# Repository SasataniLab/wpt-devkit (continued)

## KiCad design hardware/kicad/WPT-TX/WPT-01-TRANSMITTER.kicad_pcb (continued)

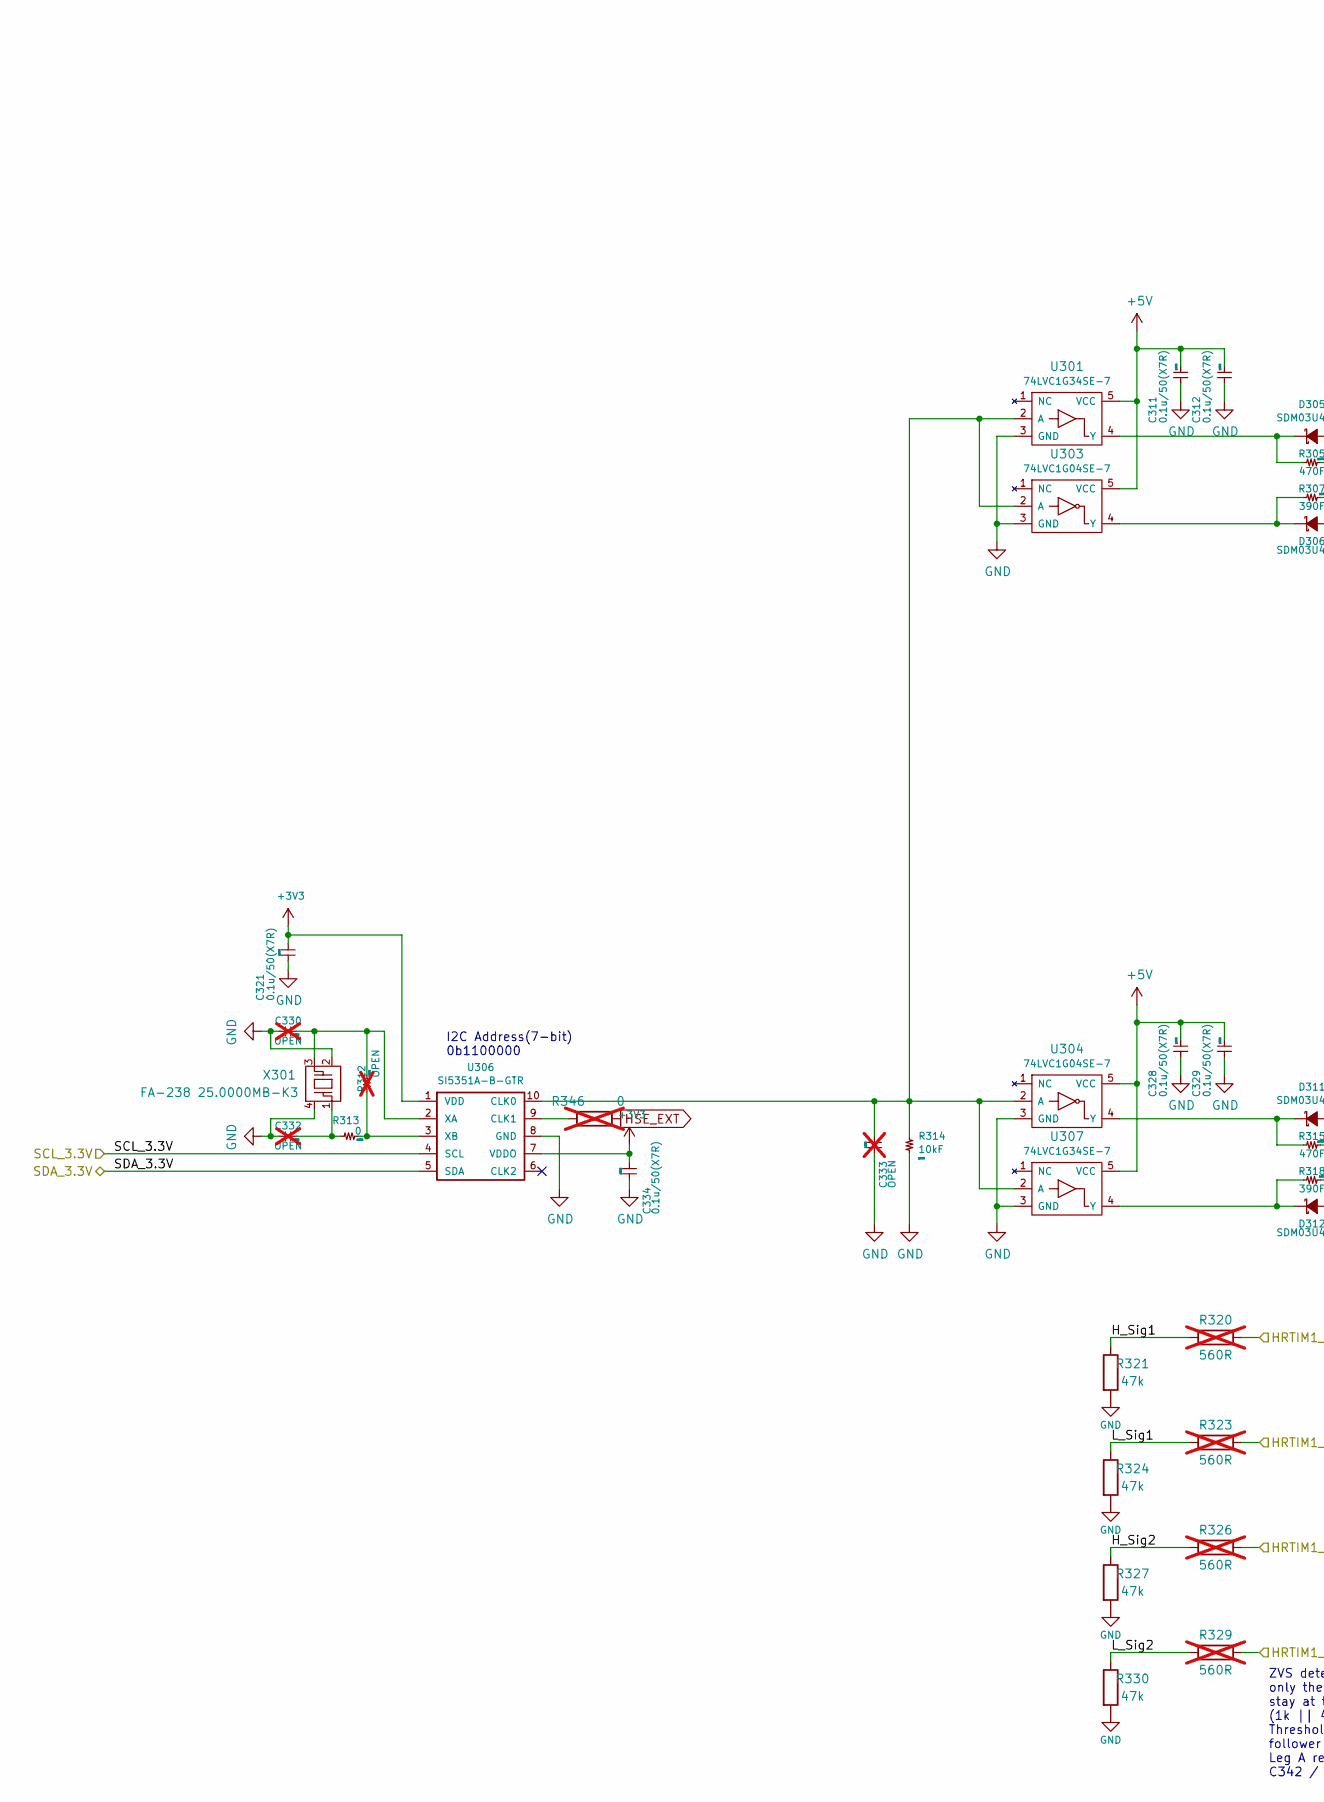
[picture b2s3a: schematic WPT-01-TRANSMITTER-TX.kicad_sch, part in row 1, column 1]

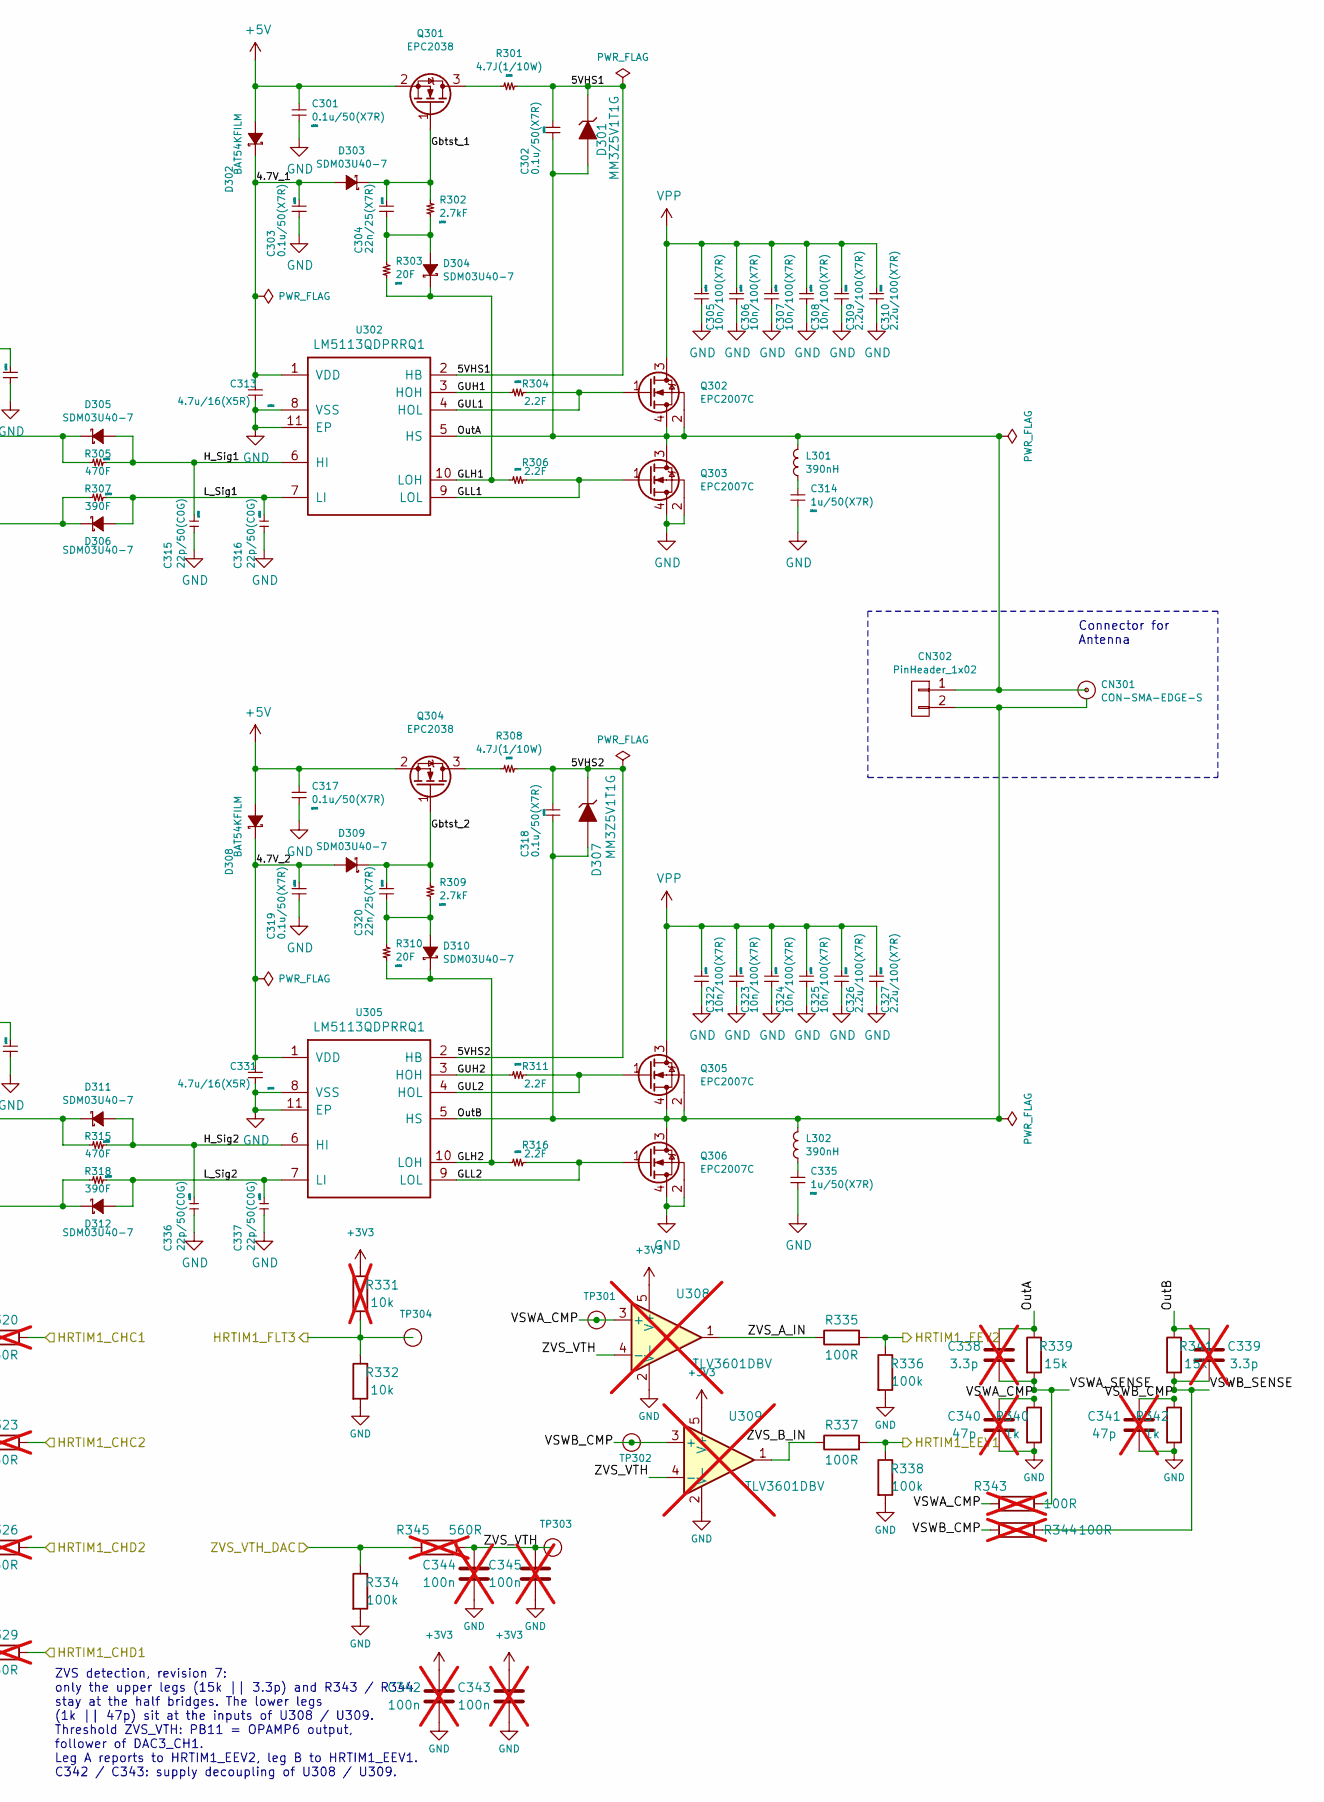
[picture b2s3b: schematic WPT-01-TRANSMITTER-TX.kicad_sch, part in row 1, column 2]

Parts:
C301, C302, C303, C311, C312, C317, C318, C319, C321, C328, C329, C334: 0.1u/50(X7R); GRM15; Manufacturer Part Number GCM155R71H104KE02D
C304, C320: 22n/25(X7R); GRM15; Manufacturer Part Number CC0402KRX7R8BB223
C305, C306, C307, C308, C322, C323, C324, C325: 10n/100(X7R); GRM18; Manufacturer Part Number CL10B103KC8WPNC
C309, C310, C326, C327: 2.2u/100(X7R); GRM32; Manufacturer Part Number CL32B225KCJZW6E
C313, C331: 4.7u/16(X5R); GRM15; Manufacturer Part Number CL05A475MO5NUNC
C314, C335: 1u/50(X7R); GRM21; Manufacturer Part Number CL21B105KBFNNNG
C315, C316, C336, C337: 22p/50(C0G); GRM15; Manufacturer Part Number GCM1555C1H220JA16D
C330, C332: OPEN; GRM15; Manufacturer Part Number GRM15; not fitted
C333: OPEN; GRM15; Manufacturer Part Number CC0402; not fitted
C338, C339: 3.3p; C_0402_1005Metric; Manufacturer Part Number GJM1555C1H3R3BB01D; not fitted
C340, C341: 47p; C_0402_1005Metric; Manufacturer Part Number GCM1555C1H470GA16D; not fitted
C342, C343, C344, C345: 100n; C_0402_1005Metric; Manufacturer Part Number GCM155R71H104KE02D; not fitted
CN301: CON-SMA-EDGE-S; Manufacturer Part Number CON-SMA-EDGE-S
CN302: PinHeader_1x02; ULO-PH409-1x2SX1; Manufacturer Part Number 61300211121
D301, D307: MM3Z5V1T1G; SOD-323; Manufacturer Part Number MM3Z5V1T1G
D302, D308: BAT54KFILM; SOD-523F_STMicroelectronics; Manufacturer Part Number BAT54KFILM
D303, D304, D305, D306, D309, D310, D311, D312: SDM03U40-7; SOD-523F_Diodes; Manufacturer Part Number SDM03U40-7
L301, L302: 390nH; 2929SQ; Manufacturer Part Number 2929SQ-391JEC
Q301, Q304: EPC2038; Manufacturer Part Number EPC2038
Q302, Q303, Q305, Q306: EPC2007C; Manufacturer Part Number EPC2007C
R301, R308: 4.7J(1/10W); R_0402; Manufacturer Part Number ERJ-2GEJ4R7X
R302, R309: 2.7kF; R_0402; Manufacturer Part Number RC0402FR-072K7L
R303, R310: 20F; R_0402; Manufacturer Part Number RC0402FR-0720RL
R304, R306, R311, R316: 2.2F; R_0402; Manufacturer Part Number RC0402FR-072R2L
R305, R315: 470F; R_0603; Manufacturer Part Number RC0603FR-07470RL
R307, R318: 390F; R_0603; Manufacturer Part Number RC0603FR-07390RL
R312: OPEN; R_0402; Manufacturer Part Number RC0402; not fitted
R313: 0; R_0402; Manufacturer Part Number RC0402FR-070RL
R314: 10kF; R_0402; Manufacturer Part Number RC0402FR-0710KL
R320, R323, R326, R329, R345: 560R; R_0402_1005Metric; Manufacturer Part Number RC0402FR-07560RL; not fitted
R321, R324, R327, R330: 47k; R_0402_1005Metric; Manufacturer Part Number RC0402FR-0747KL
R331: 10k; R_0402_1005Metric; Manufacturer Part Number RC0402FR-0710KL; not fitted
R332: 10k; R_0402_1005Metric; Manufacturer Part Number RC0402FR-0710KL
R334, R336, R338: 100k; R_0402_1005Metric; Manufacturer Part Number RC0402FR-07100KL
R335, R337: 100R; R_0402_1005Metric; Manufacturer Part Number RC0402FR-07100RL
R339, R341: 15k; R_0402_1005Metric; Manufacturer Part Number ERJ-PA2F1502X
R340, R342: 1k; R_0402_1005Metric; Manufacturer Part Number RC0402FR-071KL
R343, R344: 100R; R_0402_1005Metric; Manufacturer Part Number RC0402FR-07100RL; not fitted
R346: 0; R_0402_1005Metric; Manufacturer Part Number RC0402FR-070RL; not fitted
TP301, TP302, TP303, TP304: TP1.0; TP_1mm
U301, U307: 74LVC1G34SE-7; SOT-353_SC-70-5_Diodes; Manufacturer Part Number 74LVC1G34SE-7
U302, U305: LM5113QDPRRQ1; Texas_S-PWSON-N10_ThermalVias; Manufacturer Part Number LM5113QDPRRQ1
U303, U304: 74LVC1G04SE-7; SOT-353_SC-70-5_Diodes; Manufacturer Part Number 74LVC1G04SE-7
U306: SI5351A-B-GTR; Siliconlabs_MSOP-10_3x3mm_Pitch0.5mm; Manufacturer Part Number SI5351A-B-GTR
U308, U309: TLV3601DBV; SOT-23-5; Manufacturer Part Number TLV3601DBVR; not fitted
X301: FA-238 25.0000MB-K3; FA-238; Manufacturer Part Number FA-238 25.0000MB-K3

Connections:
+3V3: C321.1, C334.1, C342.1, C343.1, R331.1, U306.1 (VDD), U306.7 (VDDO), U308.5 (V+), U309.5 (V+); also elsewhere on the board
+5V: C301.1, C311.1, C312.1, C317.1, C328.1, C329.1, D302.2 (A), D308.2 (A), Q301.2 (S), Q304.2 (S), U301.5 (VCC), U303.5 (VCC), U304.5 (VCC), U307.5 (VCC); also elsewhere on the board
/HRTIM1_CHC1: R320.2; also elsewhere on the board
/HRTIM1_CHC2: R323.2; also elsewhere on the board
/HRTIM1_CHD1: R329.2; also elsewhere on the board
/HRTIM1_CHD2: R326.2; also elsewhere on the board
/HRTIM1_EEV1: R337.2, R338.1; also elsewhere on the board
/HRTIM1_EEV2: R335.2, R336.1; also elsewhere on the board
/HRTIM1_FLT3: R331.2, R332.1, TP304.1; also elsewhere on the board
/WPT-01-TRANSMITTER-POWER/SCL_3.3V: U306.4 (SCL); also elsewhere on the board
/WPT-01-TRANSMITTER-POWER/SDA_3.3V: U306.5 (SDA); also elsewhere on the board
/WPT-01-TRANSMITTER-TX/4.7V_1: C303.1, C313.1, D302.1 (C), D303.2 (A), U302.1 (VDD)
/WPT-01-TRANSMITTER-TX/4.7V_2: C319.1, C331.1, D308.1 (C), D309.2 (A), U305.1 (VDD)
/WPT-01-TRANSMITTER-TX/5VHS1: C302.1, D301.1 (K), R301.1, U302.2 (HB)
/WPT-01-TRANSMITTER-TX/5VHS2: C318.1, D307.1 (K), R308.1, U305.2 (HB)
/WPT-01-TRANSMITTER-TX/GLH1: D304.1 (C), R303.1, R306.2, U302.10 (LOH)
/WPT-01-TRANSMITTER-TX/GLH2: D310.1 (C), R310.1, R316.2, U305.10 (LOH)
/WPT-01-TRANSMITTER-TX/GLL1: Q303.1 (G), R306.1, U302.9 (LOL)
/WPT-01-TRANSMITTER-TX/GLL2: Q306.1 (G), R316.1, U305.9 (LOL)
/WPT-01-TRANSMITTER-TX/GUH1: R304.2, U302.3 (HOH)
/WPT-01-TRANSMITTER-TX/GUH2: R311.2, U305.3 (HOH)
/WPT-01-TRANSMITTER-TX/GUL1: Q302.1 (G), R304.1, U302.4 (HOL)
/WPT-01-TRANSMITTER-TX/GUL2: Q305.1 (G), R311.1, U305.4 (HOL)
/WPT-01-TRANSMITTER-TX/Gbtst_1: C304.1, D303.1 (C), Q301.1 (G), R302.2
/WPT-01-TRANSMITTER-TX/Gbtst_2: C320.1, D309.1 (C), Q304.1 (G), R309.2
/WPT-01-TRANSMITTER-TX/H_Sig1: C315.1, D305.2 (A), R305.1, R320.1, R321.1, U302.6 (HI)
/WPT-01-TRANSMITTER-TX/H_Sig2: C336.1, D311.2 (A), R315.1, R326.1, R327.1, U305.6 (HI)
/WPT-01-TRANSMITTER-TX/L_Sig1: C316.1, D306.2 (A), R307.1, R323.1, R324.1, U302.7 (LI)
/WPT-01-TRANSMITTER-TX/L_Sig2: C337.1, D312.2 (A), R318.1, R329.1, R330.1, U305.7 (LI)
/WPT-01-TRANSMITTER-TX/OutA: C302.2, C338.1, CN301.1, CN302.1, D301.2 (A), L301.2, Q302.2 (S), Q302.4 (S), Q303.3 (D), R339.1, U302.5 (HS)
/WPT-01-TRANSMITTER-TX/OutB: C318.2, C339.1, CN301.2, CN302.2, D307.2 (A), L302.2, Q305.2 (S), Q305.4 (S), Q306.3 (D), R341.1, U305.5 (HS)
/WPT-01-TRANSMITTER-TX/VSWA_CMP: C340.1, R340.1, R343.1, TP301.1, U308.3 (+)
/WPT-01-TRANSMITTER-TX/VSWA_SENSE: C338.2, R339.2, R343.2
/WPT-01-TRANSMITTER-TX/VSWB_CMP: C341.1, R342.1, R344.1, TP302.1, U309.3 (+)
/WPT-01-TRANSMITTER-TX/VSWB_SENSE: C339.2, R341.2, R344.2
/WPT-01-TRANSMITTER-TX/ZVS_A_IN: R335.1, U308.1
/WPT-01-TRANSMITTER-TX/ZVS_B_IN: R337.1, U309.1
/WPT-01-TRANSMITTER-TX/ZVS_VTH: C344.1, C345.1, R345.2, TP303.1, U308.4 (-), U309.4 (-)
/ZVS_VTH_DAC: R334.1, R345.1; also elsewhere on the board
GND: C301.2, C303.2, C305.2, C306.2, C307.2, C308.2, C309.2, C310.2, C311.2, C312.2, C313.2, C314.2, C315.2, C316.2, C317.2, C319.2, C321.2, C322.2, C323.2, C324.2, C325.2, C326.2, C327.2, C328.2, C329.2, C330.1, C331.2, C332.1, C333.2, C334.2, C335.2, C336.2, C337.2, C340.2, C341.2, C342.2, C343.2, C344.2, C345.2, Q303.2 (S), Q303.4 (S), Q306.2 (S), Q306.4 (S), R314.1, R321.2, R324.2, R327.2, R330.2, R332.2, R334.2, R336.2, R338.2, R340.2, R342.2, U301.3 (GND), U302.8 (VSS), U302.11 (EP), U303.3 (GND), U304.3 (GND), U305.8 (VSS), U305.11 (EP), U306.8 (GND), U307.3 (GND), U308.2 (V-), U309.2 (V-), X301.2, X301.4; also elsewhere on the board
HSE_EXT: R346.2; also elsewhere on the board
unnamed: C314.1, L301.1
unnamed: C332.2, R313.2, X301.1
unnamed: C335.1, L302.1
unnamed: C304.2, D304.2 (A), R302.1, R303.2
unnamed: D305.1 (C), R305.2, U301.4 (Y)
unnamed: D306.1 (C), R307.2, U303.4 (Y)
unnamed: C320.2, D310.2 (A), R309.1, R310.2
unnamed: D311.1 (C), R315.2, U304.4 (Y)
unnamed: D312.1 (C), R318.2, U307.4 (Y)
unnamed: Q301.3 (D), R301.2
unnamed: Q304.3 (D), R308.2
unnamed: C333.1, R314.2, U301.2 (A), U303.2 (A), U304.2 (A), U306.10 (CLK0), U307.2 (A)
unnamed: R346.1, U306.9 (CLK1)
unnamed: C330.2, R312.2, U306.2 (XA), X301.3
unnamed: R312.1, R313.1, U306.3 (XB)
VPP: C305.1, C306.1, C307.1, C308.1, C309.1, C310.1, C322.1, C323.1, C324.1, C325.1, C326.1, C327.1, Q302.3 (D), Q305.3 (D); also elsewhere on the board

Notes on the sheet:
Connector for Antenna
I2C Address(7-bit) 0b1100000
ZVS detection, revision 7: only the upper legs (15k || 3.3p) and R343 / R344 stay at the half bridges. The lower legs (1k || 47p) sit at the inputs of U308 / U309. Threshold ZVS_VTH: PB11 = OPAMP6 output, follower of DAC3_CH1. Leg A reports to HRTIM1_EEV2, leg B to HRTIM1_EEV1. C342 / C343: supply 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

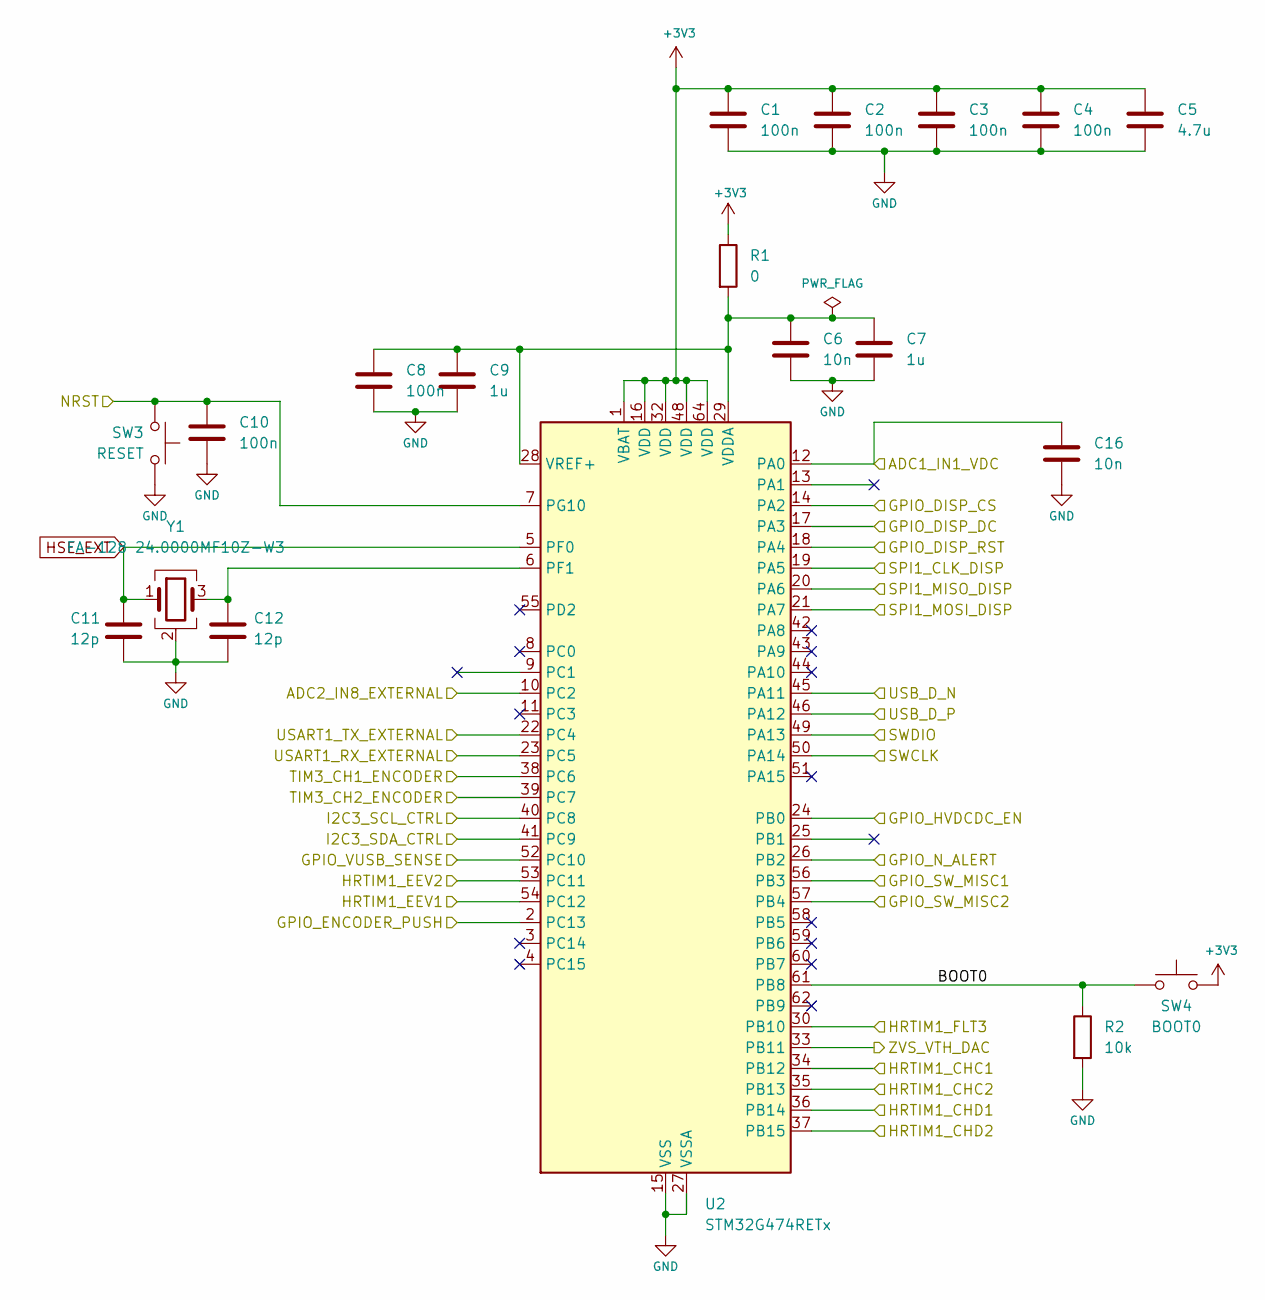
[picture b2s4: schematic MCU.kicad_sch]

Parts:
C1, C2, C3, C4, C8, C10: 100n; C_0402_1005Metric; Manufacturer Part Number GCM155R71H104KE02D
C5: 4.7u; C_0402_1005Metric; Manufacturer Part Number GRM155R60J475ME47D
C6, C16: 10n; C_0402_1005Metric; Manufacturer Part Number CC0402KRX7R9BB103
C7, C9: 1u; C_0402_1005Metric; Manufacturer Part Number CL05A105KA5NQNC
C11, C12: 12p; C_0402_1005Metric; Manufacturer Part Number GRM1555C1H120JA01D
R1: 0; R_0402_1005Metric; Manufacturer Part Number RC0402FR-070RL
R2: 10k; R_0402_1005Metric; Manufacturer Part Number RC0402FR-0710KL
SW3: RESET; SW_SPST_B3U-3000P-B_BoardEdge; Manufacturer Part Number B3U-3000P-B
SW4: BOOT0; SW_SPST_B3U-3000P-B_BoardEdge; Manufacturer Part Number B3U-3000P-B
U2: STM32G474RETx; LQFP-64_10x10mm_P0.5mm; Manufacturer Part Number STM32G474RET6
Y1: FA-128 24.0000MF10Z-W3; Crystal_SMD_SeikoEpson_FA128-4Pin_2.0x1.6mm; Manufacturer Part Number FA-128 24.0000MF10Z-W3

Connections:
+3V3: C1.1, C2.1, C3.1, C4.1, C5.1, R1.1, SW4.1, U2.1 (VBAT), U2.16 (VDD), U2.32 (VDD), U2.48 (VDD), U2.64 (VDD); also elsewhere on the board
/GPIO_VUSB_SENSE: U2.52 (PC10); also elsewhere on the board
/HRTIM1_CHC1: U2.34 (PB12); also elsewhere on the board
/HRTIM1_CHC2: U2.35 (PB13); also elsewhere on the board
/HRTIM1_CHD1: U2.36 (PB14); also elsewhere on the board
/HRTIM1_CHD2: U2.37 (PB15); also elsewhere on the board
/HRTIM1_EEV1: U2.54 (PC12); also elsewhere on the board
/HRTIM1_EEV2: U2.53 (PC11); also elsewhere on the board
/HRTIM1_FLT3: U2.30 (PB10); also elsewhere on the board
/HV_EN_MCU: U2.24 (PB0); also elsewhere on the board
/MCU/ADC2_IN8_EXTERNAL: U2.10 (PC2); also elsewhere on the board
/MCU/BOOT0: R2.1, SW4.2, U2.61 (PB8)
/MCU/GPIO_DISP_CS: U2.14 (PA2); also elsewhere on the board
/MCU/GPIO_DISP_DC: U2.17 (PA3); also elsewhere on the board
/MCU/GPIO_DISP_RST: U2.18 (PA4); also elsewhere on the board
/MCU/GPIO_ENCODER_PUSH: U2.2 (PC13); also elsewhere on the board
/MCU/GPIO_SW_MISC1: U2.56 (PB3); also elsewhere on the board
/MCU/GPIO_SW_MISC2: U2.57 (PB4); also elsewhere on the board
/MCU/NRST: C10.1, SW3.1, U2.7 (PG10); also elsewhere on the board
/MCU/SPI1_CLK_DISP: U2.19 (PA5); also elsewhere on the board
/MCU/SPI1_MISO_DISP: U2.20 (PA6); also elsewhere on the board
/MCU/SPI1_MOSI_DISP: U2.21 (PA7); also elsewhere on the board
/MCU/SWCLK: U2.50 (PA14); also elsewhere on the board
/MCU/SWDIO: U2.49 (PA13); also elsewhere on the board
/MCU/TIM3_CH1_ENCODER: U2.38 (PC6); also elsewhere on the board
/MCU/TIM3_CH2_ENCODER: U2.39 (PC7); also elsewhere on the board
/MCU/USART1_RX_EXTERNAL: U2.23 (PC5); also elsewhere on the board
/MCU/USART1_TX_EXTERNAL: U2.22 (PC4); also elsewhere on the board
/USB_D_N: U2.45 (PA11); also elsewhere on the board
/USB_D_P: U2.46 (PA12); also elsewhere on the board
/WPT-01-TRANSMITTER-POWER/ADC_VDC: C16.1, U2.12 (PA0); also elsewhere on the board
/WPT-01-TRANSMITTER-POWER/SCL: U2.40 (PC8); also elsewhere on the board
/WPT-01-TRANSMITTER-POWER/SDA: U2.41 (PC9); also elsewhere on the board
/WPT-01-TRANSMITTER-POWER/~ALERT: U2.26 (PB2); also elsewhere on the board
/ZVS_VTH_DAC: U2.33 (PB11); also elsewhere on the board
GND: C1.2, C2.2, C3.2, C4.2, C5.2, C6.2, C7.2, C8.2, C9.2, C10.2, C11.2, C12.2, C16.2, R2.2, SW3.2, U2.15 (VSS), U2.27 (VSSA), U2.31 (VSS), U2.47 (VSS), U2.63 (VSS), Y1.2 (G), Y1.4 (G); also elsewhere on the board
HSE_EXT: C11.1, U2.5 (PF0), Y1.1; also elsewhere on the board
unnamed: C12.1, U2.6 (PF1), Y1.3
unnamed: C6.1, C7.1, C8.1, C9.1, R1.2, U2.28 (VREF+), U2.29 (VDDA)

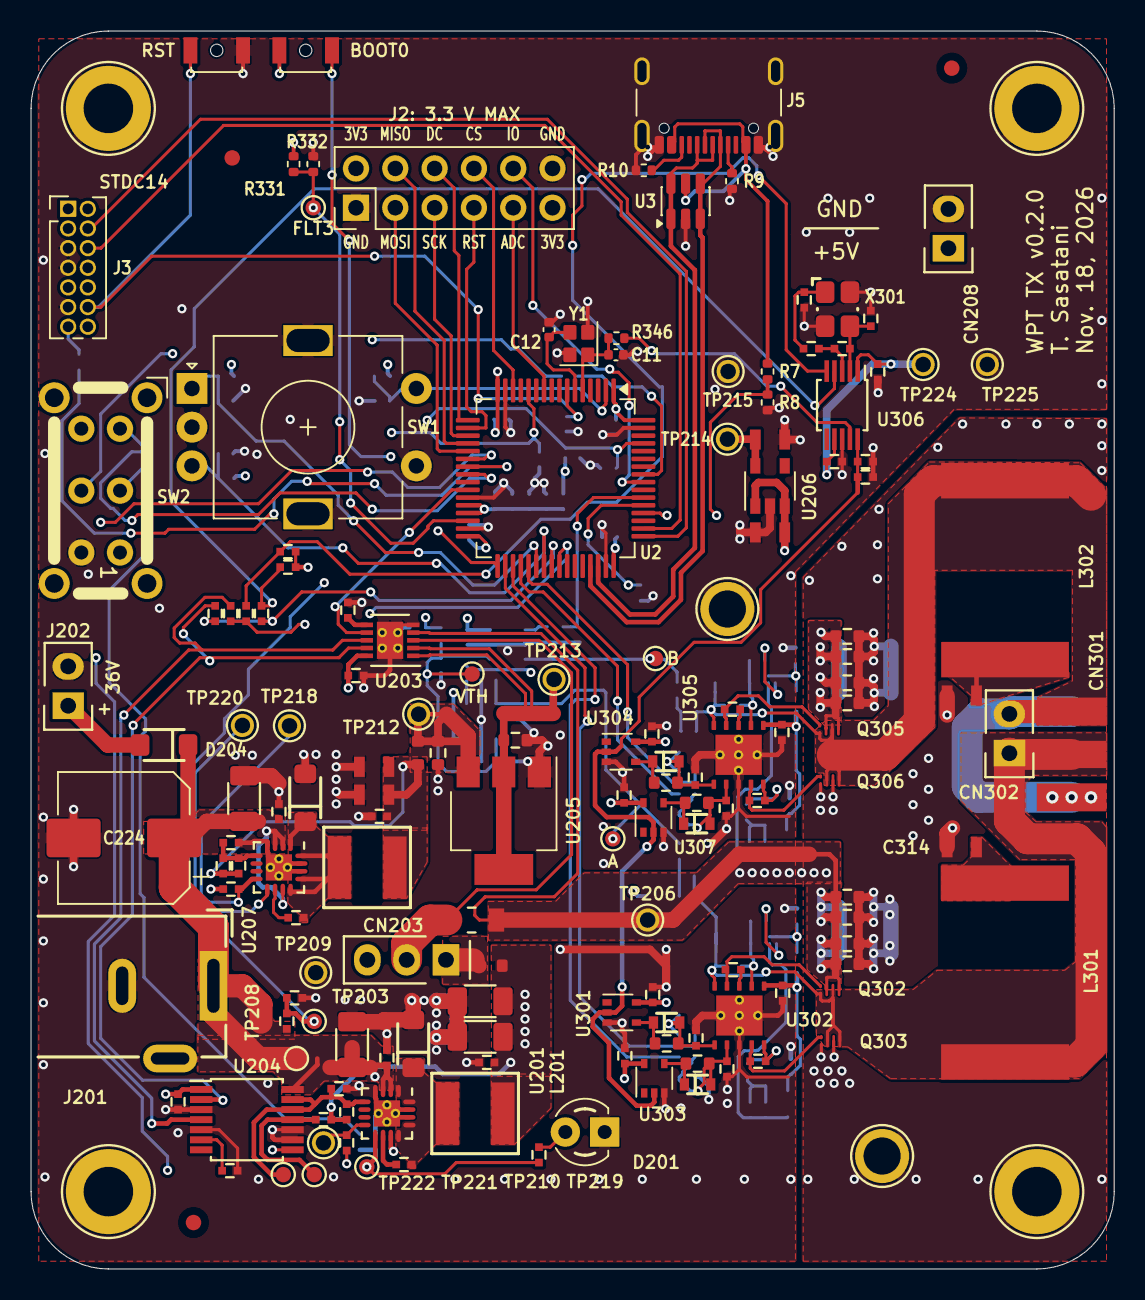
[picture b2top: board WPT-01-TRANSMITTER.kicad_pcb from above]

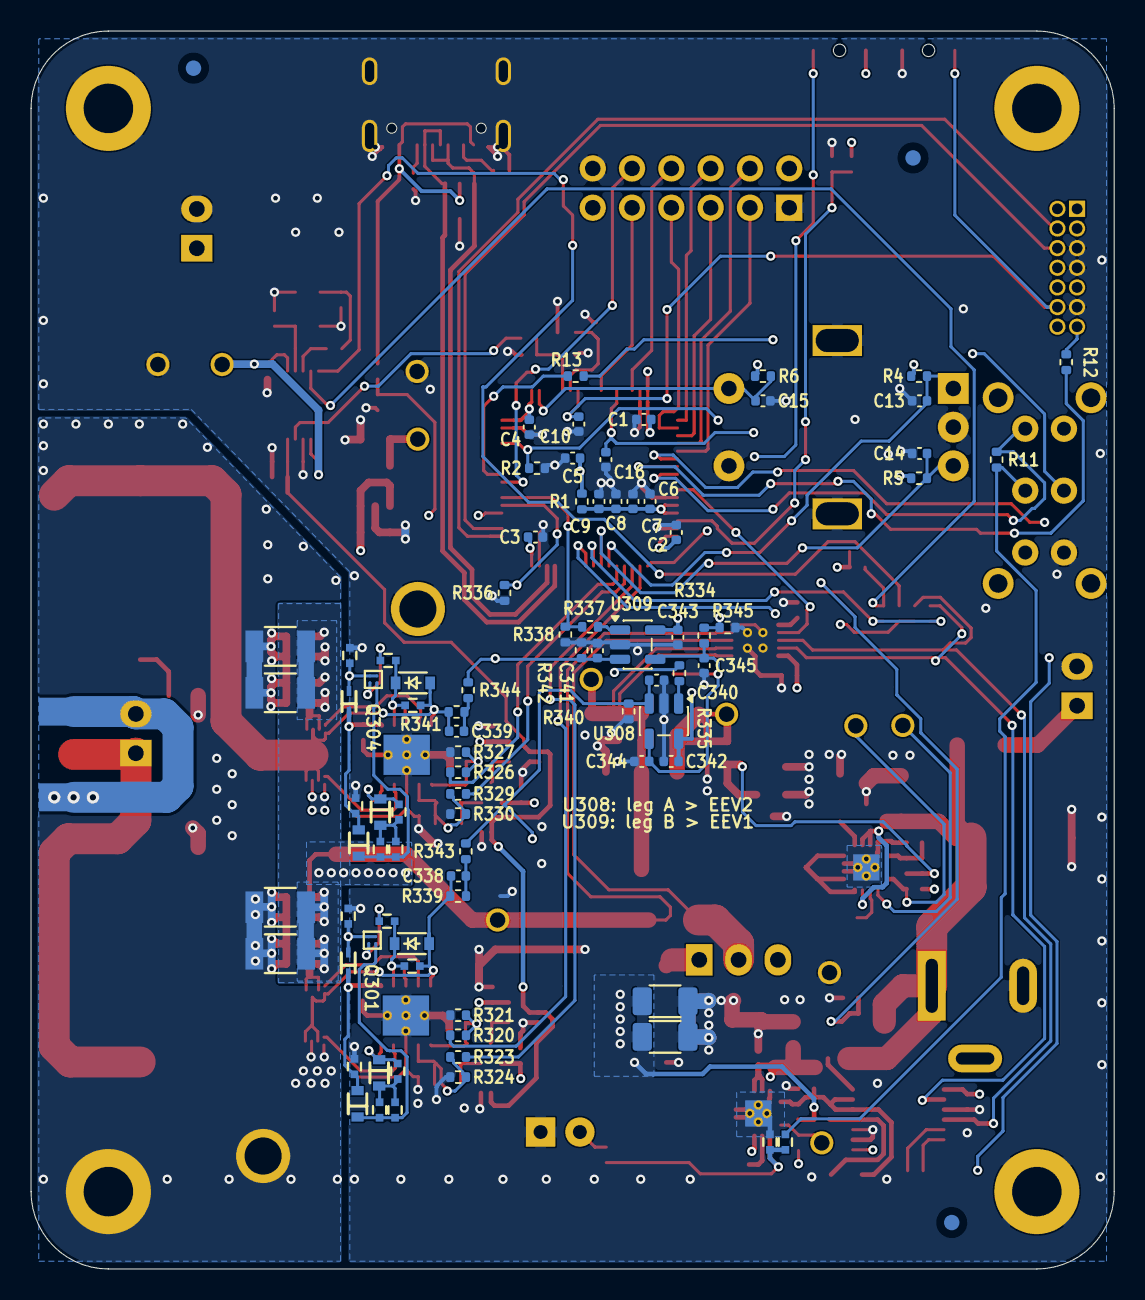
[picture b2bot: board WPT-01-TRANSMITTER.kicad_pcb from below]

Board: 4 copper layers, 70.0 x 80.0 mm, 242 parts (87 on the bottom side), 114 nets.

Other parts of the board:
FID1, FID2, FID3, FID4, FID5, FID6: Fiducial; Fiducial_1mm_Mask2mm
